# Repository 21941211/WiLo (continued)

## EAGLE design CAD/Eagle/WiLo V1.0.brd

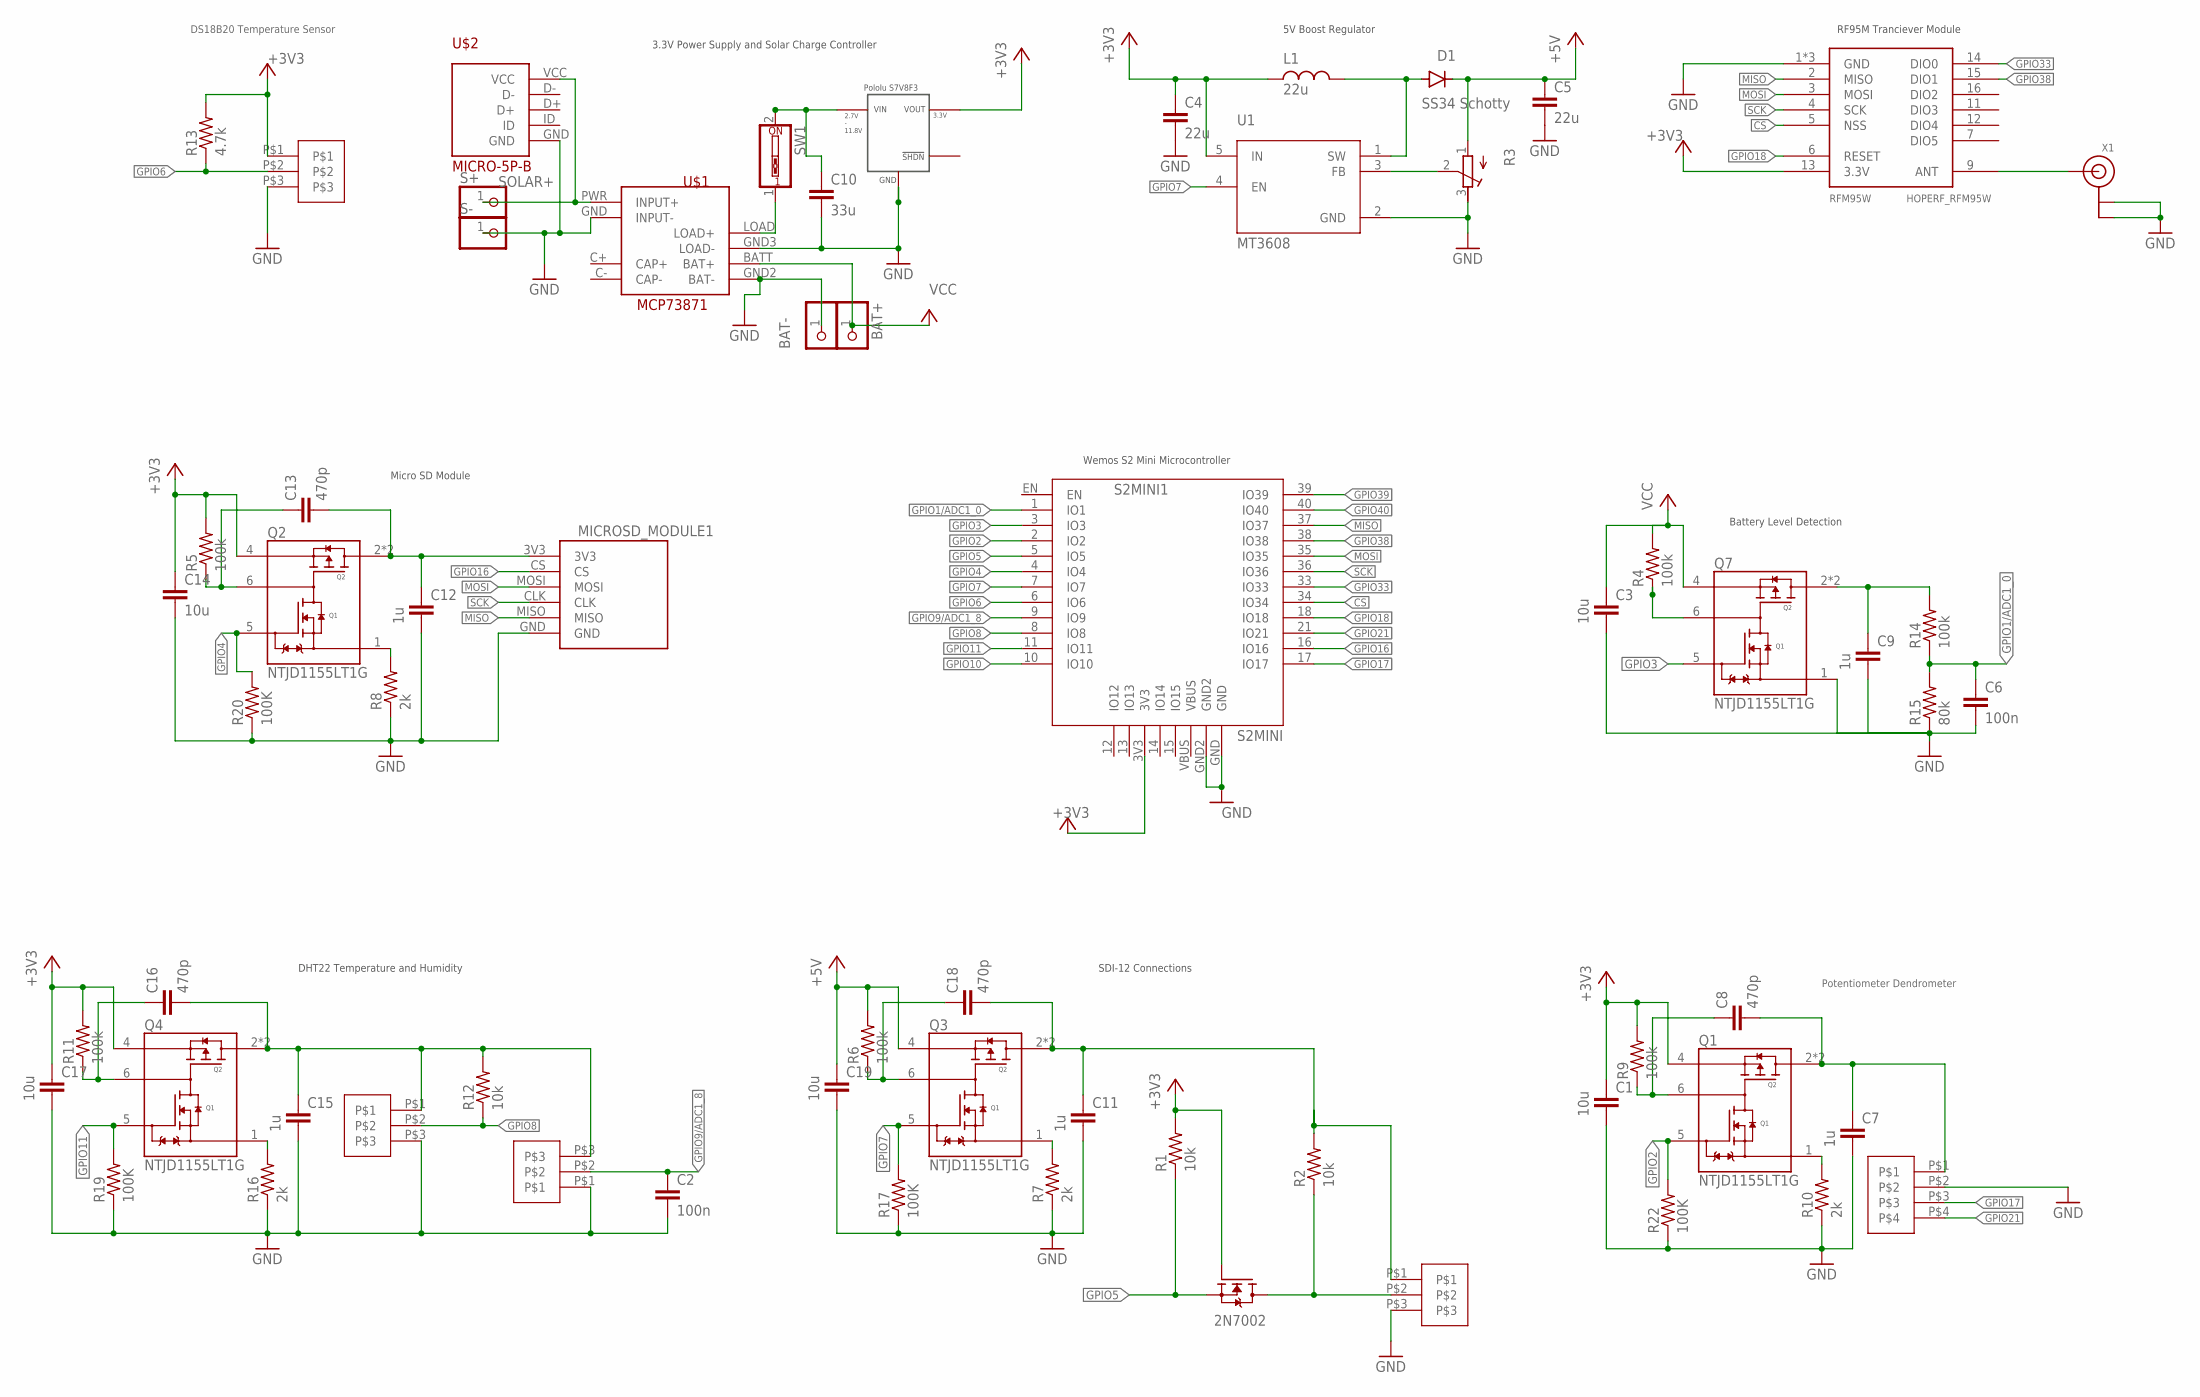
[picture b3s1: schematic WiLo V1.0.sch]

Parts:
BAT+: PINHD-1X1; 1X01
BAT-: PINHD-1X1; 1X01
C1, C3, C14, C17, C19: 10u; C0805
C2, C6: 100n; C0805
C4, C5: 22u; C0805
C7, C9, C11, C12, C15: 1u; C0805
C8, C13, C16, C18: 470p; C0805
C10: 33u; C025-024X044
D1: SS34 Schotty; DO214BA
L1: 22u; SLF7045
MICROSD_MODULE1: GENERIC_MICROSD_MODULE
Q1, Q2, Q3, Q4, Q7: NTJD1155LT1G; TRANS_NTJD1155LT1G
Q6: 2N7002; SOT95P240X111-3N
R1, R2, R12: 10k; R0603
R3: R-TRIMM3296W; RTRIM3296W
R4, R5, R6, R9, R11, R14: 100k; R0603
R7, R8, R10, R16: 2k; R0603
R13: 4.7k; R0603
R15: 80k; R0603
R17, R19, R20, R22: 100K; R0603
RFM95W: HOPERF_RFM95W
S2MINI1: S2MINI
S+: PINHD-1X1; 1X01
S-: PINHD-1X1; 1X01
SW1: SW_DIP-1; EDG-01
U1: MT3608; SOT95P280X145-6N
U$1: MCP73871
U$2: MICRO-5P-B
U$3: S7V8F3
U$4, U$5, U$6, U$7: 3PIN_2.54_SCREW
U$8: 4PIN_2.54_SCREW
X1: ANTENNA_U.FL; U.FL

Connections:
5V_SDI12: C11.1, C18.2, Q3.2 (D2), Q3.3 (D2), R2.2, U$7.P$1
+3V3: C1.1, C4.1, C14.1, C17.1, L1.+ (1), Q1.4 (S2), Q2.4 (S2), Q4.4 (S2), Q6.1 (G), R1.2, R5.2, R9.2, R11.2, R13.2, RFM95W.13 (3.3V), S2MINI1.3V3, U1.5 (IN), U$3.VOUT, U$4.P$1
+5V: C5.1, C19.1, D1.C, Q3.4 (S2), R3.1 (A), R6.2
CS: RFM95W.5 (NSS), S2MINI1.34 (IO34)
GND: BAT-.1, C1.2, C2.2, C3.2, C4.2, C5.2, C6.2, C7.2, C9.2, C10.2, C11.2, C12.2, C14.2, C15.2, C17.2, C19.2, MICROSD_MODULE1.GND, Q7.1 (S1), R3.3 (E), R7.1, R8.1, R10.1, R15.1, R16.1, R17.1, R19.1, R20.1, R22.1, RFM95W.1 (GND), RFM95W.8 (GND), RFM95W.10 (GND), S2MINI1.GND, S2MINI1.GND2, S-.1, U1.2 (GND), U$1.GND (INPUT-), U$1.GND2 (BAT-), U$1.GND3 (LOAD-), U$2.GND, U$3.GND, U$4.P$3, U$5.P$3, U$6.P$1, U$7.P$3, U$8.P$2, X1.1 (GND), X1.2 (GND)
GPIO1/ADC1_0: C6.1, R14.1, R15.2, S2MINI1.1 (IO1)
GPIO2: Q1.5 (G1), R22.2, S2MINI1.2 (IO2)
GPIO3: Q7.5 (G1), S2MINI1.3 (IO3)
GPIO4: Q2.5 (G1), R20.2, S2MINI1.4 (IO4)
GPIO5: Q6.2 (S), R1.1, S2MINI1.5 (IO5)
GPIO6: R13.1, S2MINI1.6 (IO6), U$4.P$2
GPIO7: Q3.5 (G1), R17.2, S2MINI1.7 (IO7), U1.4 (EN)
GPIO8: R12.1, S2MINI1.8 (IO8), U$5.P$2
GPIO9/ADC1_8: C2.1, S2MINI1.9 (IO9), U$6.P$2
GPIO10: S2MINI1.10 (IO10)
GPIO11: Q4.5 (G1), R19.2, S2MINI1.11 (IO11)
GPIO16: MICROSD_MODULE1.CS, S2MINI1.16 (IO16)
GPIO17: S2MINI1.17 (IO17), U$8.P$3
GPIO18: RFM95W.6 (RESET), S2MINI1.18 (IO18)
GPIO21: S2MINI1.21 (IO21), U$8.P$4
GPIO33: RFM95W.14 (DIO0), S2MINI1.33 (IO33)
GPIO38: RFM95W.15 (DIO1), S2MINI1.38 (IO38)
GPIO39: S2MINI1.39 (IO39)
GPIO40: S2MINI1.40 (IO40)
MISO: MICROSD_MODULE1.MISO, RFM95W.2 (MISO), S2MINI1.37 (IO37)
MOSI: MICROSD_MODULE1.MOSI, RFM95W.3 (MOSI), S2MINI1.35 (IO35)
unnamed: RFM95W.9 (ANT), X1.3 (SIGNAL)
unnamed: C18.1, Q3.6 (D1/G2), R6.1
unnamed: Q3.1 (S1), R7.2
unnamed: C8.1, Q1.6 (D1/G2), R9.1
unnamed: C7.1, C8.2, Q1.2 (D2), Q1.3 (D2), U$8.P$1
unnamed: Q1.1 (S1), R10.2
unnamed: D1.A, L1.- (2), U1.1 (SW)
unnamed: C10.1, SW1.2, U$3.VIN
unnamed: C9.1, Q7.2 (D2), Q7.3 (D2), R14.2
unnamed: R3.2 (S), U1.3 (FB)
unnamed: C13.1, Q2.6 (D1/G2), R5.1
unnamed: C12.1, C13.2, MICROSD_MODULE1.3V3, Q2.2 (D2), Q2.3 (D2)
unnamed: Q2.1 (S1), R8.2
unnamed: Q7.6 (D1/G2), R4.1
unnamed: C16.1, Q4.6 (D1/G2), R11.1
unnamed: C15.1, C16.2, Q4.2 (D2), Q4.3 (D2), R12.2, U$5.P$1, U$6.P$3
unnamed: Q4.1 (S1), R16.2
unnamed: Q6.3 (D), R2.1, U$7.P$2
unnamed: SW1.1, U$1.LOAD (LOAD+)
SCK: MICROSD_MODULE1.CLK, RFM95W.4 (SCK), S2MINI1.36 (IO36)
SOLAR+: S+.1, U$1.PWR (INPUT+), U$2.VCC
VCC: BAT+.1, C3.1, Q7.4 (S2), R4.2, U$1.BATT (BAT+)

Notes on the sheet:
3.3V Power Supply and Solar Charge Controller
RF95M Tranciever Module
Wemos S2 Mini Microcontroller
Battery Level Detection
Micro SD Module
DS18B20 Temperature Sensor
Potentiometer Dendrometer
DHT22 Temperature and Humidity
SDI-12 Connections
5V Boost Regulator

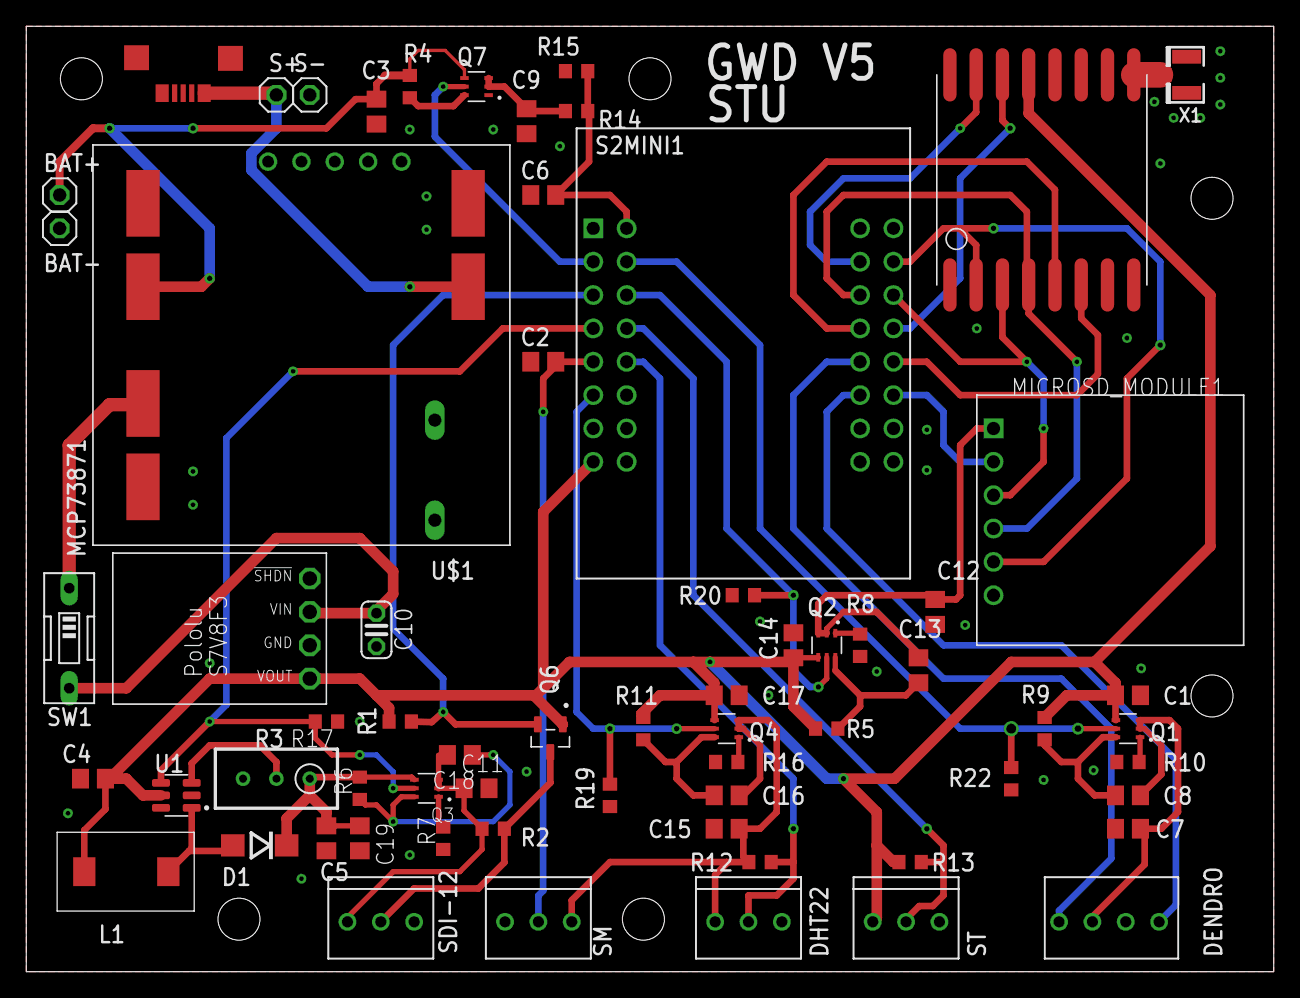
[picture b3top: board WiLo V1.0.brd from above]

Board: 2 copper layers, 95.0 x 72.0 mm, 65 parts (0 on the bottom side), 45 nets.

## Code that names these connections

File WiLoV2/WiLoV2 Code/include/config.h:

//File names
#define DEFAULT_FILE_NAME "/Measurements.csv"
#define FILE_NAME_SDI12_60 "/SDI_12_60cm_Measurements.csv"
#define FILE_NAME_SDI12_90 "/SDI_12_90cm_Measurements.csv"
#define FILE_NAME_CS655 "/SDI_12_CS655_Measurements.csv"
#define FILE_NAME_I2C_MUX_SAPFLOW "/I2C_Mux_Sapflow_Measurements.csv"
#define FILE_NAME_I2C_MUX_DENDROMETER "/I2C_Mux_Dendrometer_Measurements.csv"
#define FILE_NAME_SYSPARAMS "/parameters.txt"
#define FILE_NAME_PAYLOAD_CONFIG "/PayloadConfig.txt"
#define FILE_NAME_TIME "/DateTime.csv"


//LoRa Pins
#define LORA_EN_PIN 4
#define LORA_SCK_PIN 36
#define LORA_MISO_PIN 37
#define LORA_MOSI_PIN 35
#define LORA_CS_PIN 34
#define LORA_RST_PIN 18
#define LORA_DIO0_PIN 33
#define LORA_DIO1_PIN 38
#define LORA_SPI 1


//RTC pins
#define RTC_EN_PIN 15

//DHT22 and SM enable pin
#define DHT22_SM_ST_EN_PIN 8


//Soil moistures sensor pins
#define SM_ADC_PIN 1

// DHT22 Pins
#define DHT22_DATA_PIN 6

// Temperature sensor pins
#define SOIL_TEMPERATURE_DATA_PIN 2

// Battery level detector pins
#define BATTERY_LVL_ADC_EN_PIN 5
#define BATTERY_ADC_PIN 3

//Sapflow sensor pins
#define HEAT_PULSE_EN_PIN 7

// I2C Pins (For communication with I2C Mux, Dendrometers and Sapflow sensors)
#define I2C_PORT_EN_PIN 13
#define I2C_SDA 17
#define I2C_SCL 21



//Dendrometer pins
//#define DENDROMETER_PIN 8
//#define DENDROMETER_ENABLE_PIN GPIO_NUM_2//4


//Onboard LED pin
//#define DEBUG_LED_PIN 15

//SDI-12 drill and drop sensor pins
#define SDI12_EN_PIN 9
#define SDI12_DATA_PIN 14

//SD card defines
#define SD_SCK_PIN  36
#define SD_MISO_PIN  37
#define SD_MOSI_PIN  35
#define SD_CS_PIN    16
#define SD_SPI 2
#define SD_ENABLE_PIN 10


//Debug LED pin
#define LED_PIN 15

// Number of samples taken for each dendrometer
#define DENDRO_SAMPLE_SIZE 10


//Sapflow sensor heat pulse state measuring time
#define SAMPLE_TIME_BEFORE_HP 5000 //5 seconds
#define SAMPLE_TIME_DURING_HP 10000 // 10 seconds
#define SF_DELAY 25000 // 25 seconds
#define SAMPLE_TIME_AFTER_HP 10000 // 10 seconds

//Deep sleep times
#define uS_TO_S_FACTOR 1000000  /* Conversion factor for micro seconds to seconds */
#define WILO_MAX_CYCLE_TIME  1200      /* Maximum cycle time of the WiLo in seconds. Wilo is active for time x, deep sleep is thus WILO_MAX_CYCLE_TIME-x */
#define DEEP_SLEEP_LORA_TEST  120      /* Time ESP32 will go to sleep (in seconds) */
#define WILO_MAX_CYCLE_TIME_WITH_SDI12_CONNECTED  1200     /* Maximum cycle time of the WiLo in seconds, if SDI12 is connected. Wilo is active for time x, deep sleep is thus WILO_MAX_CYCLE_TIME-x */
#define LIGHT_SLEEP 5 /*When a transmission fails, WILO goes into light sleep for 5 seconds*/
#define LORA_CONNECT_TIMEOUT 60 /*During this time, the system tries to reconnect to LoRa gateway after a failed transmission attempt. If timeout is reached. WiLo goes into deep sleep*/


//WiFi Timeout
#define WIFI_TIMEOUT 15000 // Timeout for WiFi connection in milliseconds

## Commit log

2025-04-16 WiLo Parameter file backups
    The files contained herein are text files, required by each WiLo in the IMPACT OAL deployment.
    you will see for each WiLo number (WiLo-xxx) there is a folder containing the LoRa keys. These need to be transferred to the SD card of each WiLo for LoRa integration. Ensure that SD cards are format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
2025-04-16 Inital Source Commit
2025-04-16 Test
2025-04-16 Another test
2025-04-16 OTA Firmware upgrade code added
2025-04-16 Added More Documentation
2025-04-17 Fixed OTA bugs, fixed deep sleep bugs
2025-04-21 payload formatter backup
2025-04-23 Added a firware extraction script
2025-04-29 OTA SoftAP and SF error flags
2025-05-02 Added datasheet
2025-05-02 Updated payload formatter
2025-05-05 Update LICENSE
2025-07-03 Updated folder structure
2025-07-03 Added Eagle source, gerber, BOM and centroid files for WiLoV2
2025-07-03 Updated DigiDendro, created PCB manufacturing files
2025-07-07 Updated WiLoV2 source code and PCBWay files
2025-08-04 Added WiLo V2 dcumentation
2025-09-05 rtc code uncommented and data timestamped before SD write
2025-11-14 MUX RTC fixes, SDI-12 bug fixes
2025-11-14 WiFi re-enabled, firmware.bin updated
2026-04-23 Added sapflow timer between heatpulse and after heatpulse measurements
2026-04-23 Added sapflow delay to WiLo V2
2026-04-24 Bug fixes
2026-04-24 Added flags for checking sapflow calculations
2026-04-24 Syntax error fix
2026-04-24 SDI-12 tests
2026-05-05 Sapflow Driver Fixes, one-shot measurement mode instead of continuous.
2026-05-26 Added longer rise time delay for sapflow measurements, reduced number of samples taken
2026-05-26 Fixed not printing count T2 after to serial
2026-05-29 Fixed some typos in serial debug
2026-06-23 Bug fixes for Mux overflow
